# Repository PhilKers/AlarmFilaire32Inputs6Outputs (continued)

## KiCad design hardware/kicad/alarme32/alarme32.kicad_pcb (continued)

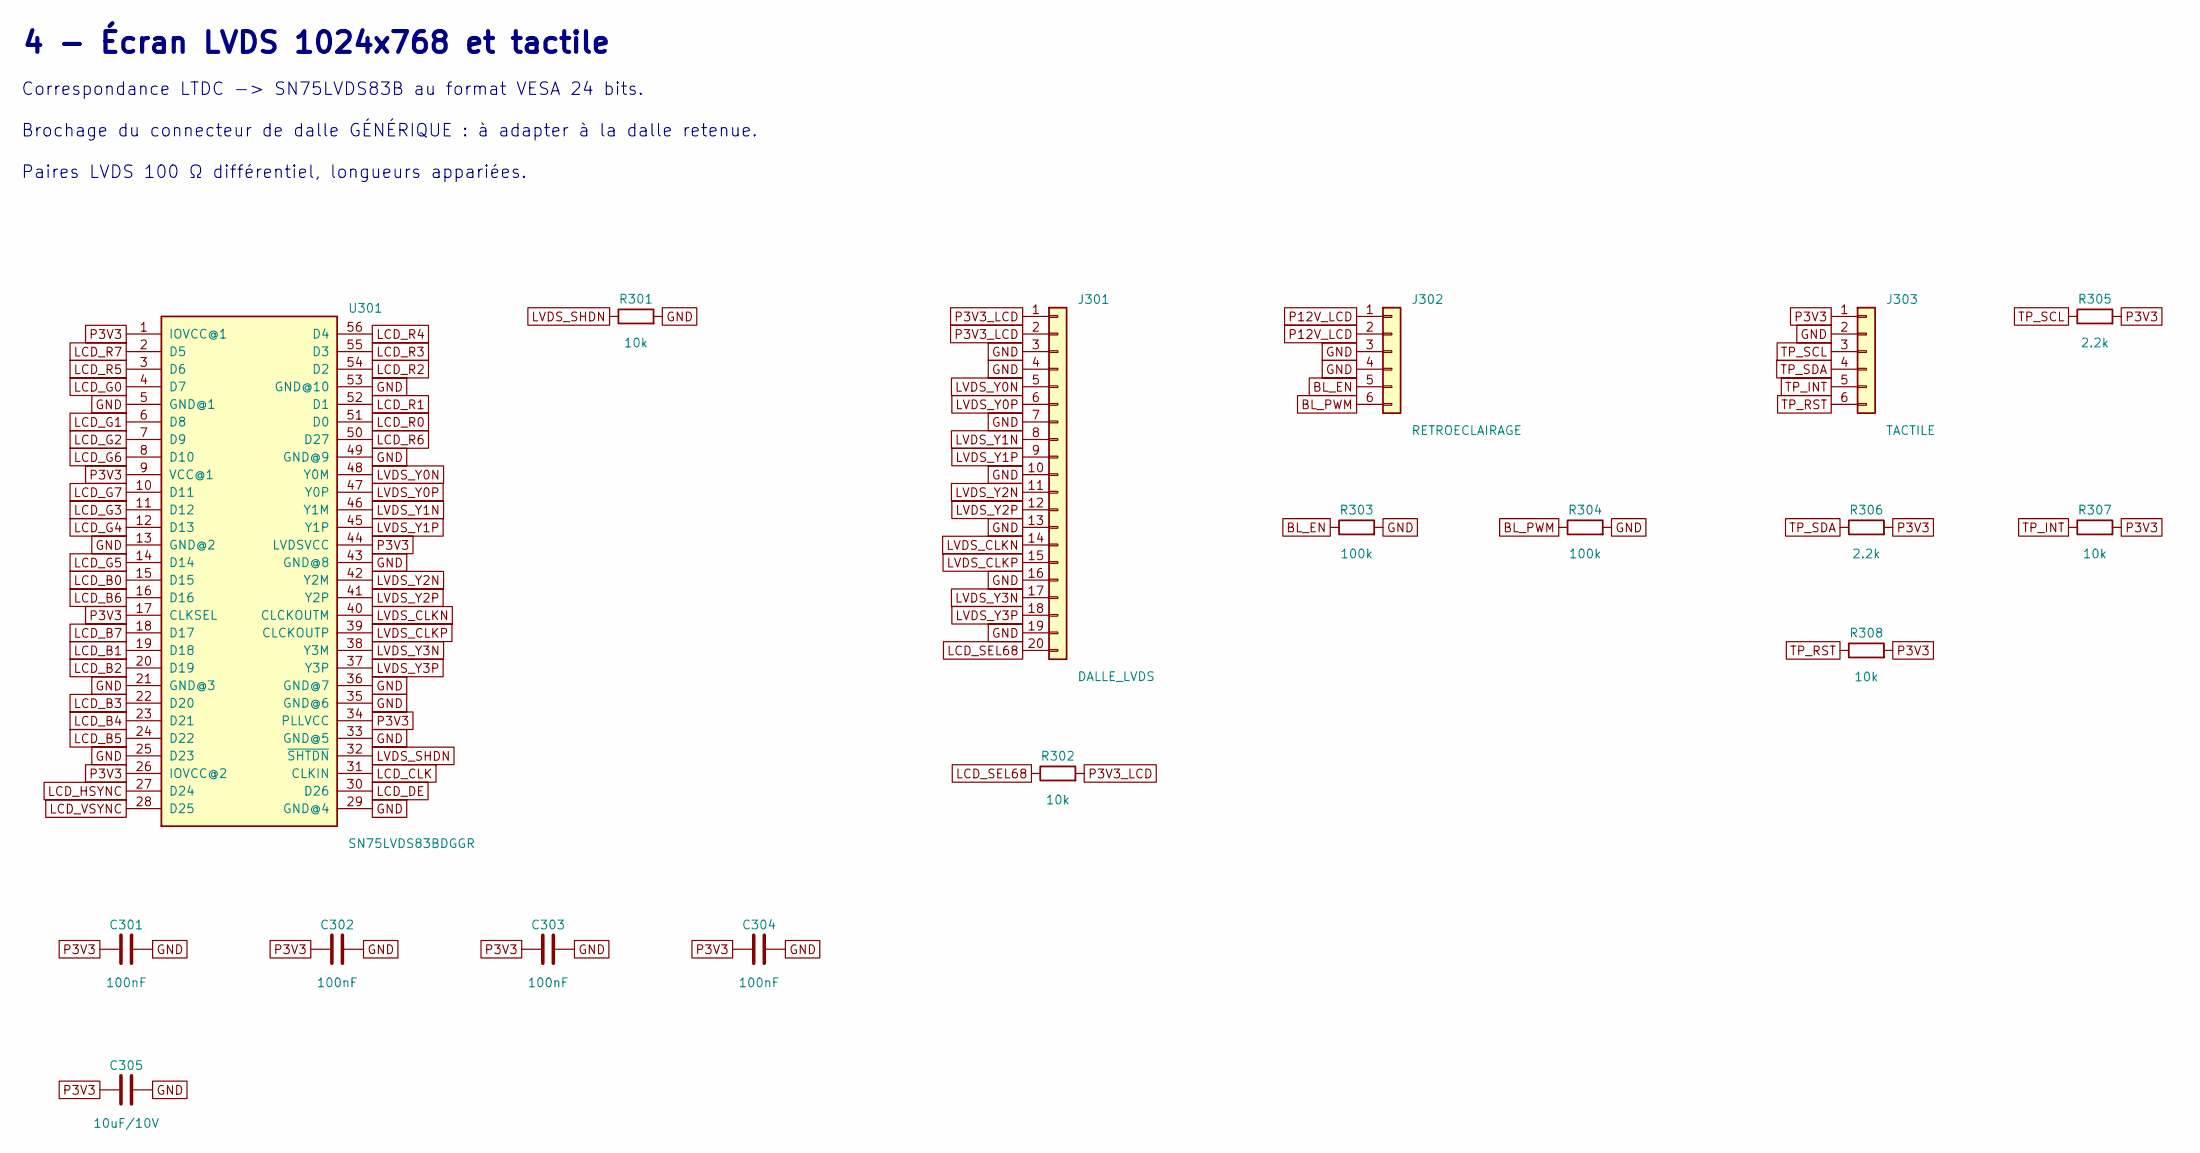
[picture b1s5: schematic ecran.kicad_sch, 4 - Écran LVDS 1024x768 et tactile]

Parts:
C301, C302, C303, C304: 100nF; C_0603_1608Metric
C305: 10uF/10V; C_0805_2012Metric
J301: DALLE_LVDS; TE_2-84952-0_1x20-1MP_P1.0mm_Horizontal
J302: RETROECLAIRAGE; JST_PH_B6B-PH-K_1x06_P2.00mm_Vertical
J303: TACTILE; Hirose_FH12-6S-0.5SH_1x06-1MP_P0.50mm_Horizontal
R301, R302, R307, R308: 10k; R_0603_1608Metric
R303, R304: 100k; R_0603_1608Metric
R305, R306: 2.2k; R_0603_1608Metric
U301: SN75LVDS83BDGGR; TSSOP-56_6.1x14mm_P0.5mm

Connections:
BL_EN: J302.5, R303.1; also elsewhere on the board
BL_PWM: J302.6, R304.1; also elsewhere on the board
GND: C301.2, C302.2, C303.2, C304.2, C305.2, J301.3, J301.4, J301.7, J301.10, J301.13, J301.16, J301.19, J302.3, J302.4, J303.2, R301.2, R303.2, R304.2, U301.5 (GND@1), U301.13 (GND@2), U301.21 (GND@3), U301.25 (D23), U301.29 (GND@4), U301.33 (GND@5), U301.35 (GND@6), U301.36 (GND@7), U301.43 (GND@8), U301.49 (GND@9), U301.53 (GND@10); also elsewhere on the board
LCD_B0: U301.15 (D15); also elsewhere on the board
LCD_B1: U301.19 (D18); also elsewhere on the board
LCD_B2: U301.20 (D19); also elsewhere on the board
LCD_B3: U301.22 (D20); also elsewhere on the board
LCD_B4: U301.23 (D21); also elsewhere on the board
LCD_B5: U301.24 (D22); also elsewhere on the board
LCD_B6: U301.16 (D16); also elsewhere on the board
LCD_B7: U301.18 (D17); also elsewhere on the board
LCD_CLK: U301.31 (CLKIN); also elsewhere on the board
LCD_DE: U301.30 (D26); also elsewhere on the board
LCD_G0: U301.4 (D7); also elsewhere on the board
LCD_G1: U301.6 (D8); also elsewhere on the board
LCD_G2: U301.7 (D9); also elsewhere on the board
LCD_G3: U301.11 (D12); also elsewhere on the board
LCD_G4: U301.12 (D13); also elsewhere on the board
LCD_G5: U301.14 (D14); also elsewhere on the board
LCD_G6: U301.8 (D10); also elsewhere on the board
LCD_G7: U301.10 (D11); also elsewhere on the board
LCD_HSYNC: U301.27 (D24); also elsewhere on the board
LCD_R0: U301.51 (D0); also elsewhere on the board
LCD_R1: U301.52 (D1); also elsewhere on the board
LCD_R2: U301.54 (D2); also elsewhere on the board
LCD_R3: U301.55 (D3); also elsewhere on the board
LCD_R4: U301.56 (D4); also elsewhere on the board
LCD_R5: U301.3 (D6); also elsewhere on the board
LCD_R6: U301.50 (D27); also elsewhere on the board
LCD_R7: U301.2 (D5); also elsewhere on the board
LCD_SEL68: J301.20, R302.1
LCD_VSYNC: U301.28 (D25); also elsewhere on the board
LVDS_CLKN: J301.14, U301.40 (CLCKOUTM)
LVDS_CLKP: J301.15, U301.39 (CLCKOUTP)
LVDS_SHDN: R301.1, U301.32 (~SHTDN); also elsewhere on the board
LVDS_Y0N: J301.5, U301.48 (Y0M)
LVDS_Y0P: J301.6, U301.47 (Y0P)
LVDS_Y1N: J301.8, U301.46 (Y1M)
LVDS_Y1P: J301.9, U301.45 (Y1P)
LVDS_Y2N: J301.11, U301.42 (Y2M)
LVDS_Y2P: J301.12, U301.41 (Y2P)
LVDS_Y3N: J301.17, U301.38 (Y3M)
LVDS_Y3P: J301.18, U301.37 (Y3P)
P3V3: C301.1, C302.1, C303.1, C304.1, C305.1, J303.1, R305.2, R306.2, R307.2, R308.2, U301.1 (IOVCC@1), U301.9 (VCC@1), U301.17 (CLKSEL), U301.26 (IOVCC@2), U301.34 (PLLVCC), U301.44 (LVDSVCC); also elsewhere on the board
P3V3_LCD: J301.1, J301.2, R302.2; also elsewhere on the board
P12V_LCD: J302.1, J302.2; also elsewhere on the board
TP_INT: J303.5, R307.1; also elsewhere on the board
TP_RST: J303.6, R308.1; also elsewhere on the board
TP_SCL: J303.3, R305.1; also elsewhere on the board
TP_SDA: J303.4, R306.1; also elsewhere on the board

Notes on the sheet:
4 - Écran LVDS 1024x768 et tactile
Correspondance LTDC -> SN75LVDS83B au format VESA 24 bits.
Brochage du connecteur de dalle GÉNÉRIQUE : à adapter à la dalle retenue.
Paires LVDS 100 Ω différentiel, longueurs appariées.

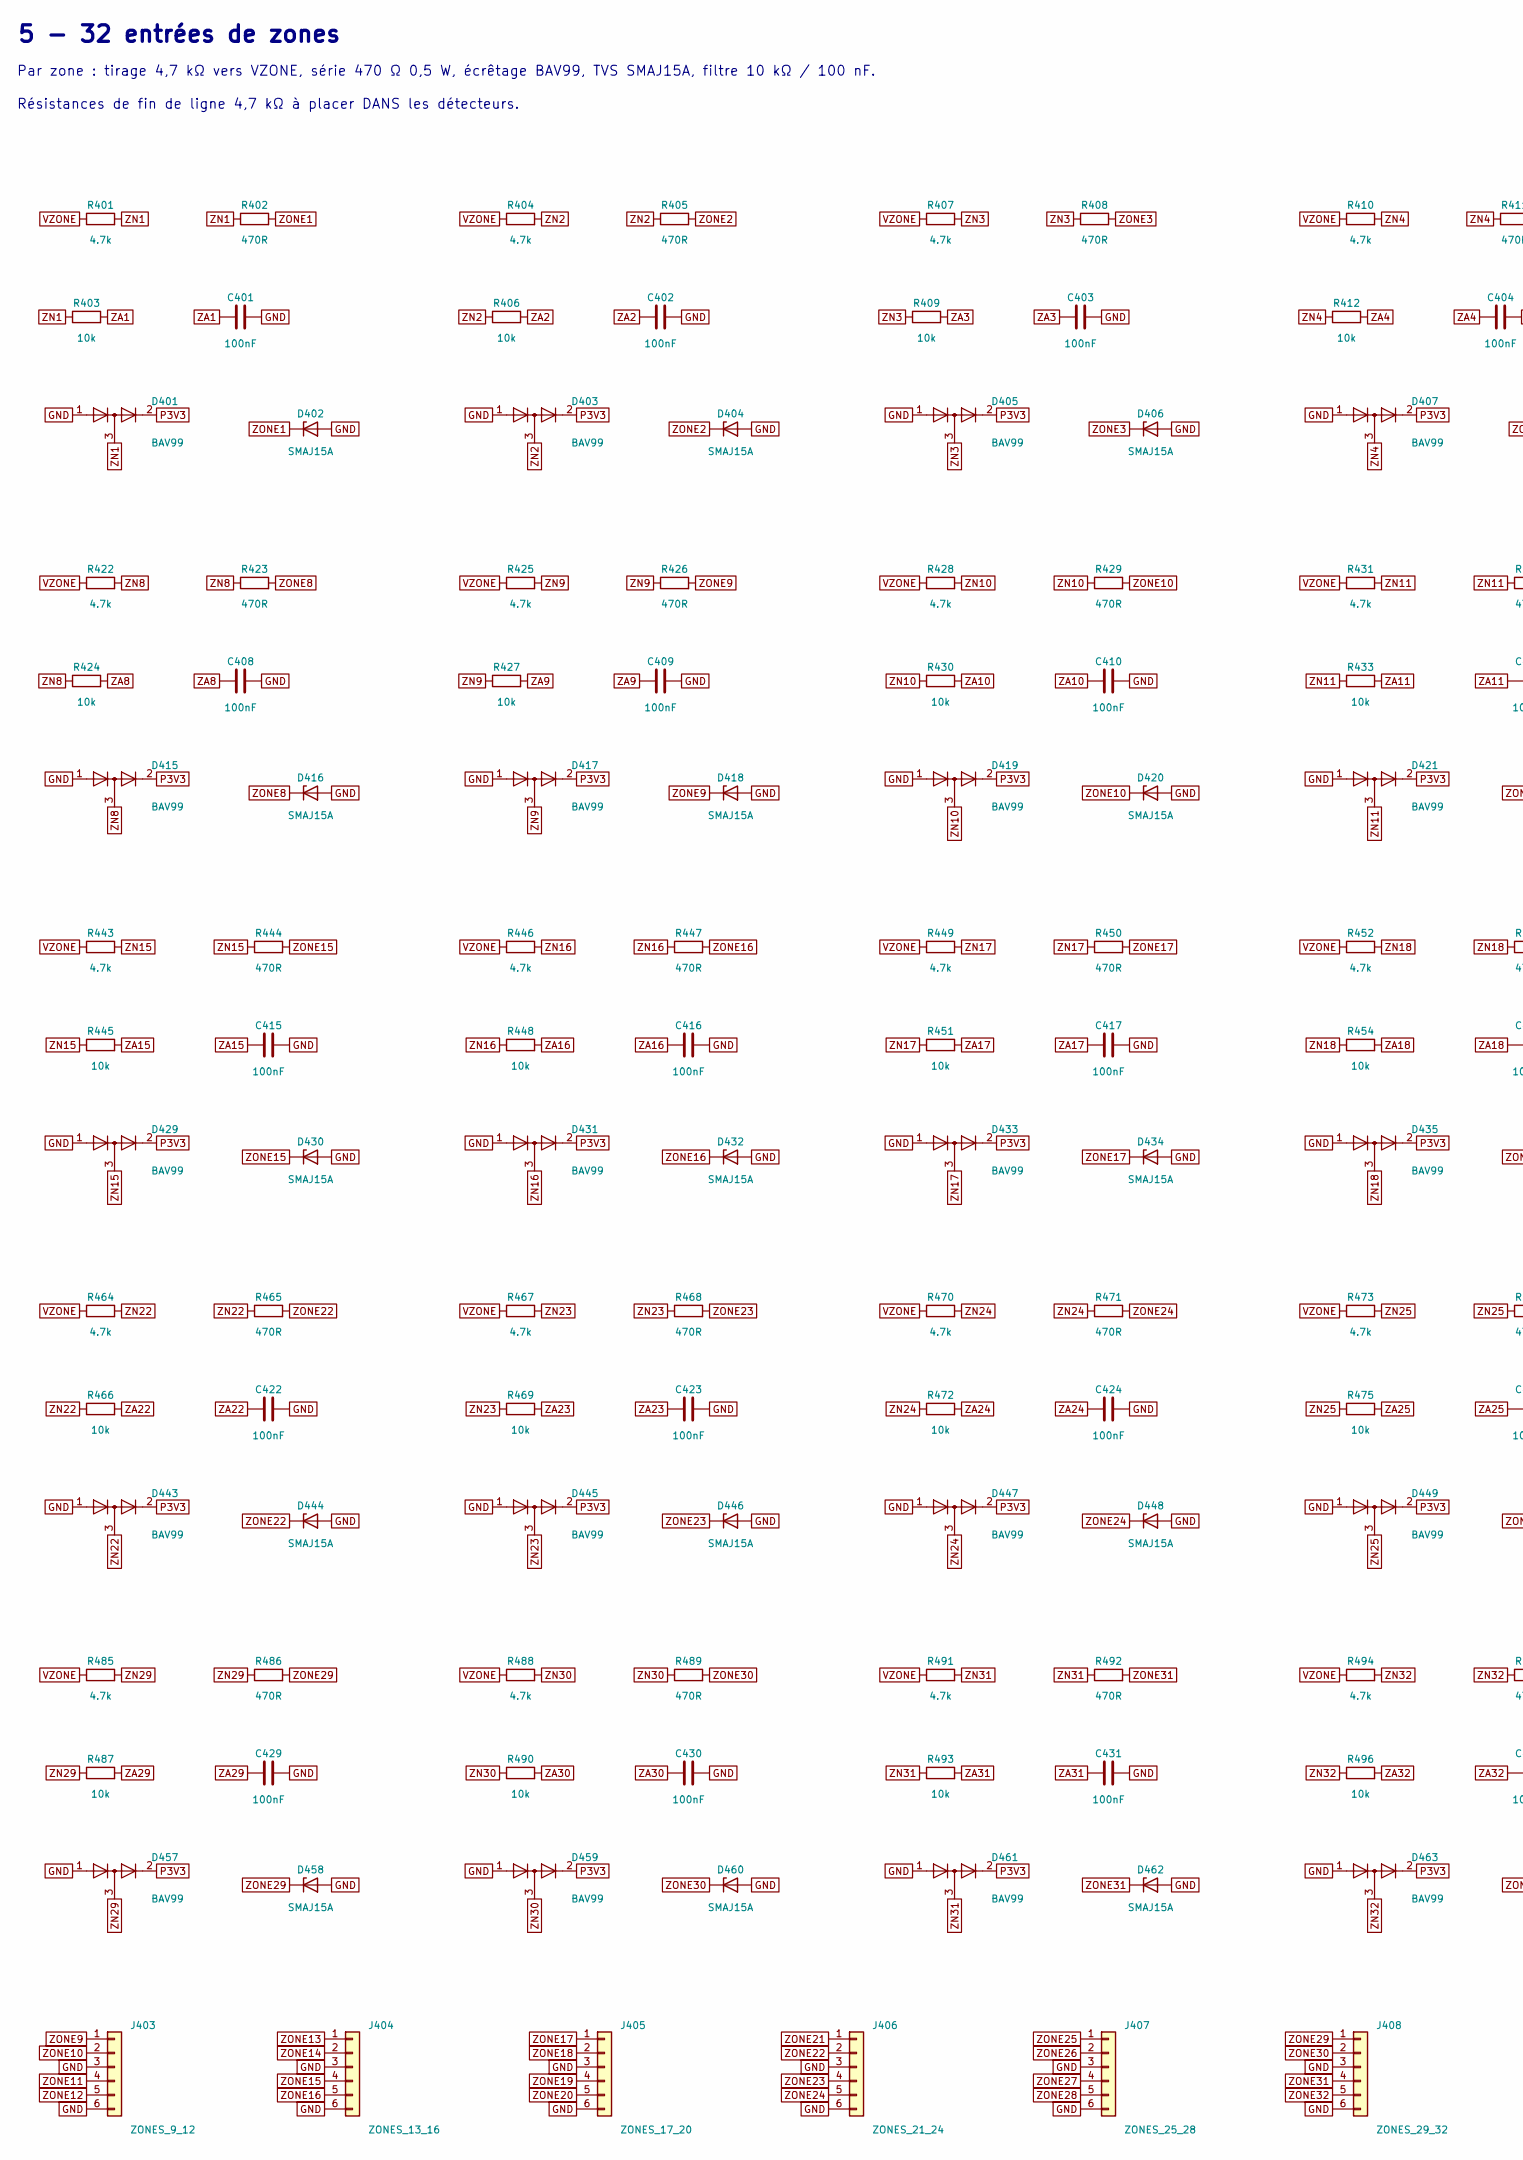
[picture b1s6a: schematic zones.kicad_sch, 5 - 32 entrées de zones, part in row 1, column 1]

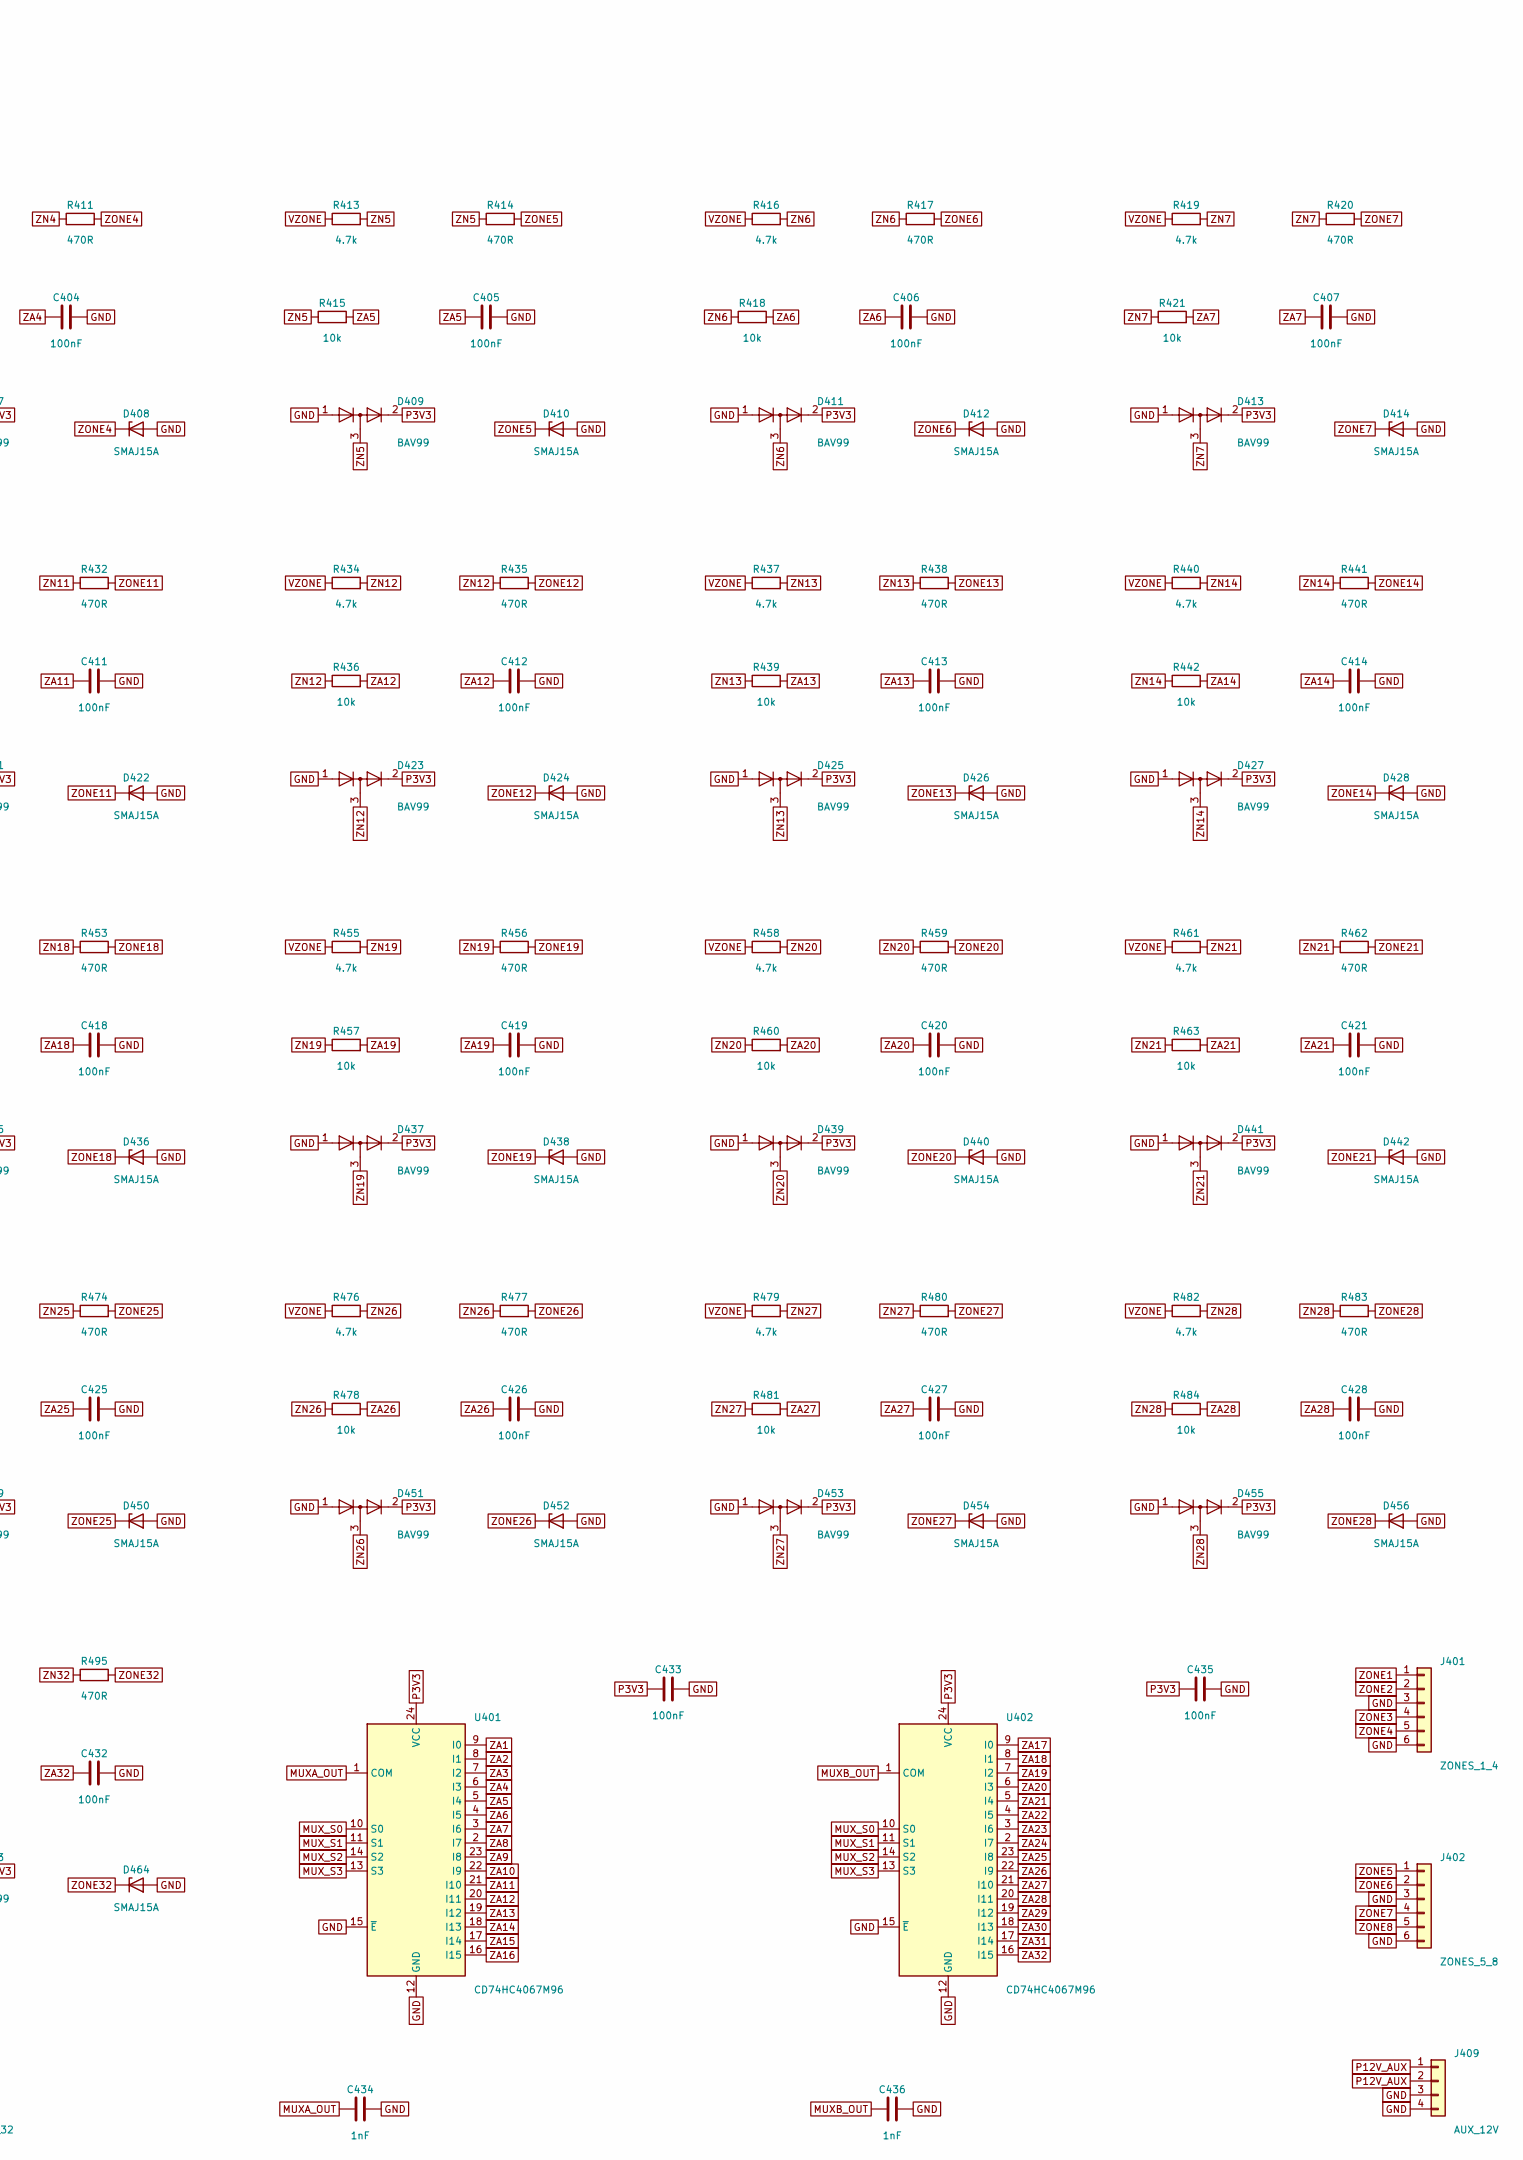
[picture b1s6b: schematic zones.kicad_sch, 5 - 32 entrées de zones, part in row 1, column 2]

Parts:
C401, C402, C403, C404, C405, C406, C407, C408, C409, C410, C411, C412, C413, C414, C415, C416, C417, C418, C419, C420, C421, C422, C423, C424, C425, C426, C427, C428, C429, C430, C431, C432, C433, C435: 100nF; C_0603_1608Metric
C434, C436: 1nF; C_0603_1608Metric
D401, D403, D405, D407, D409, D411, D413, D415, D417, D419, D421, D423, D425, D427, D429, D431, D433, D435, D437, D439, D441, D443, D445, D447, D449, D451, D453, D455, D457, D459, D461, D463: BAV99; SOT-23
D402, D404, D406, D408, D410, D412, D414, D416, D418, D420, D422, D424, D426, D428, D430, D432, D434, D436, D438, D440, D442, D444, D446, D448, D450, D452, D454, D456, D458, D460, D462, D464: SMAJ15A; D_SMA
J401: ZONES_1_4; TerminalBlock_Phoenix_MKDS-1,5-6-5.08_1x06_P5.08mm_Horizont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
J402: ZONES_5_8; TerminalBlock_Phoenix_MKDS-1,5-6-5.08_1x06_P5.08mm_Horizont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
J403: ZONES_9_12; TerminalBlock_Phoenix_MKDS-1,5-6-5.08_1x06_P5.08mm_Horizont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
J404: ZONES_13_16; TerminalBlock_Phoenix_MKDS-1,5-6-5.08_1x06_P5.08mm_Horizont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
J405: ZONES_17_20; TerminalBlock_Phoenix_MKDS-1,5-6-5.08_1x06_P5.08mm_Horizont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
J406: ZONES_21_24; TerminalBlock_Phoenix_MKDS-1,5-6-5.08_1x06_P5.08mm_Horizont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
J407: ZONES_25_28; TerminalBlock_Phoenix_MKDS-1,5-6-5.08_1x06_P5.08mm_Horizont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
J408: ZONES_29_32; TerminalBlock_Phoenix_MKDS-1,5-6-5.08_1x06_P5.08mm_Horizont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
J409: AUX_12V; TerminalBlock_Phoenix_MKDS-1,5-4-5.08_1x04_P5.08mm_Horizont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
R401, R404, R407, R410, R413, R416, R419, R422, R425, R428, R431, R434, R437, R440, R443, R446, R449, R452, R455, R458, R461, R464, R467, R470, R473, R476, R479, R482, R485, R488, R491, R494: 4.7k; R_0603_1608Metric
R402, R405, R408, R411, R414, R417, R420, R423, R426, R429, R432, R435, R438, R441, R444, R447, R450, R453, R456, R459, R462, R465, R468, R471, R474, R477, R480, R483, R486, R489, R492, R495: 470R; R_1206_3216Metric
R403, R406, R409, R412, R415, R418, R421, R424, R427, R430, R433, R436, R439, R442, R445, R448, R451, R454, R457, R460, R463, R466, R469, R472, R475, R478, R481, R484, R487, R490, R493, R496: 10k; R_0603_1608Metric
U401, U402: CD74HC4067M96; SOIC-24W_7.5x15.4mm_P1.27mm

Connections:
GND: C401.2, C402.2, C403.2, C404.2, C405.2, C406.2, C407.2, C408.2, C409.2, C410.2, C411.2, C412.2, C413.2, C414.2, C415.2, C416.2, C417.2, C418.2, C419.2, C420.2, C421.2, C422.2, C423.2, C424.2, C425.2, C426.2, C427.2, C428.2, C429.2, C430.2, C431.2, C432.2, C433.2, C434.2, C435.2, C436.2, D401.1 (K), D402.2 (A), D403.1 (K), D404.2 (A), D405.1 (K), D406.2 (A), D407.1 (K), D408.2 (A), D409.1 (K), D410.2 (A), D411.1 (K), D412.2 (A), D413.1 (K), D414.2 (A), D415.1 (K), D416.2 (A), D417.1 (K), D418.2 (A), D419.1 (K), D420.2 (A), D421.1 (K), D422.2 (A), D423.1 (K), D424.2 (A), D425.1 (K), D426.2 (A), D427.1 (K), D428.2 (A), D429.1 (K), D430.2 (A), D431.1 (K), D432.2 (A), D433.1 (K), D434.2 (A), D435.1 (K), D436.2 (A), D437.1 (K), D438.2 (A), D439.1 (K), D440.2 (A), D441.1 (K), D442.2 (A), D443.1 (K), D444.2 (A), D445.1 (K), D446.2 (A), D447.1 (K), D448.2 (A), D449.1 (K), D450.2 (A), D451.1 (K), D452.2 (A), D453.1 (K), D454.2 (A), D455.1 (K), D456.2 (A), D457.1 (K), D458.2 (A), D459.1 (K), D460.2 (A), D461.1 (K), D462.2 (A), D463.1 (K), D464.2 (A), J401.3, J401.6, J402.3, J402.6, J403.3, J403.6, J404.3, J404.6, J405.3, J405.6, J406.3, J406.6, J407.3, J407.6, J408.3, J408.6, J409.3, J409.4, U401.12 (GND), U401.15 (~E), U402.12 (GND), U402.15 (~E); also elsewhere on the board
MUXA_OUT: C434.1, U401.1 (COM); also elsewhere on the board
MUXB_OUT: C436.1, U402.1 (COM); also elsewhere on the board
MUX_S0: U401.10 (S0), U402.10 (S0); also elsewhere on the board
MUX_S1: U401.11 (S1), U402.11 (S1); also elsewhere on the board
MUX_S2: U401.14 (S2), U402.14 (S2); also elsewhere on the board
MUX_S3: U401.13 (S3), U402.13 (S3); also elsewhere on the board
P3V3: C433.1, C435.1, D401.2 (A), D403.2 (A), D405.2 (A), D407.2 (A), D409.2 (A), D411.2 (A), D413.2 (A), D415.2 (A), D417.2 (A), D419.2 (A), D421.2 (A), D423.2 (A), D425.2 (A), D427.2 (A), D429.2 (A), D431.2 (A), D433.2 (A), D435.2 (A), D437.2 (A), D439.2 (A), D441.2 (A), D443.2 (A), D445.2 (A), D447.2 (A), D449.2 (A), D451.2 (A), D453.2 (A), D455.2 (A), D457.2 (A), D459.2 (A), D461.2 (A), D463.2 (A), U401.24 (VCC), U402.24 (VCC); also elsewhere on the board
P12V_AUX: J409.1, J409.2; also elsewhere on the board
VZONE: R401.1, R404.1, R407.1, R410.1, R413.1, R416.1, R419.1, R422.1, R425.1, R428.1, R431.1, R434.1, R437.1, R440.1, R443.1, R446.1, R449.1, R452.1, R455.1, R458.1, R461.1, R464.1, R467.1, R470.1, R473.1, R476.1, R479.1, R482.1, R485.1, R488.1, R491.1, R494.1; also elsewhere on the board
ZA1: C401.1, R403.2, U401.9 (I0)
ZA2: C402.1, R406.2, U401.8 (I1)
ZA3: C403.1, R409.2, U401.7 (I2)
ZA4: C404.1, R412.2, U401.6 (I3)
ZA5: C405.1, R415.2, U401.5 (I4)
ZA6: C406.1, R418.2, U401.4 (I5)
ZA7: C407.1, R421.2, U401.3 (I6)
ZA8: C408.1, R424.2, U401.2 (I7)
ZA9: C409.1, R427.2, U401.23 (I8)
ZA10: C410.1, R430.2, U401.22 (I9)
ZA11: C411.1, R433.2, U401.21 (I10)
ZA12: C412.1, R436.2, U401.20 (I11)
ZA13: C413.1, R439.2, U401.19 (I12)
ZA14: C414.1, R442.2, U401.18 (I13)
ZA15: C415.1, R445.2, U401.17 (I14)
ZA16: C416.1, R448.2, U401.16 (I15)
ZA17: C417.1, R451.2, U402.9 (I0)
ZA18: C418.1, R454.2, U402.8 (I1)
ZA19: C419.1, R457.2, U402.7 (I2)
ZA20: C420.1, R460.2, U402.6 (I3)
ZA21: C421.1, R463.2, U402.5 (I4)
ZA22: C422.1, R466.2, U402.4 (I5)
ZA23: C423.1, R469.2, U402.3 (I6)
ZA24: C424.1, R472.2, U402.2 (I7)
ZA25: C425.1, R475.2, U402.23 (I8)
ZA26: C426.1, R478.2, U402.22 (I9)
ZA27: C427.1, R481.2, U402.21 (I10)
ZA28: C428.1, R484.2, U402.20 (I11)
ZA29: C429.1, R487.2, U402.19 (I12)
ZA30: C430.1, R490.2, U402.18 (I13)
ZA31: C431.1, R493.2, U402.17 (I14)
ZA32: C432.1, R496.2, U402.16 (I15)
ZN1: D401.3 (K), R401.2, R402.1, R403.1
ZN2: D403.3 (K), R404.2, R405.1, R406.1
ZN3: D405.3 (K), R407.2, R408.1, R409.1
ZN4: D407.3 (K), R410.2, R411.1, R412.1
ZN5: D409.3 (K), R413.2, R414.1, R415.1
ZN6: D411.3 (K), R416.2, R417.1, R418.1
ZN7: D413.3 (K), R419.2, R420.1, R421.1
ZN8: D415.3 (K), R422.2, R423.1, R424.1
ZN9: D417.3 (K), R425.2, R426.1, R427.1
ZN10: D419.3 (K), R428.2, R429.1, R430.1
ZN11: D421.3 (K), R431.2, R432.1, R433.1
ZN12: D423.3 (K), R434.2, R435.1, R436.1
ZN13: D425.3 (K), R437.2, R438.1, R439.1
ZN14: D427.3 (K), R440.2, R441.1, R442.1
ZN15: D429.3 (K), R443.2, R444.1, R445.1
ZN16: D431.3 (K), R446.2, R447.1, R448.1
ZN17: D433.3 (K), R449.2, R450.1, R451.1
ZN18: D435.3 (K), R452.2, R453.1, R454.1
ZN19: D437.3 (K), R455.2, R456.1, R457.1
ZN20: D439.3 (K), R458.2, R459.1, R460.1
ZN21: D441.3 (K), R461.2, R462.1, R463.1
ZN22: D443.3 (K), R464.2, R465.1, R466.1
ZN23: D445.3 (K), R467.2, R468.1, R469.1
ZN24: D447.3 (K), R470.2, R471.1, R472.1
ZN25: D449.3 (K), R473.2, R474.1, R475.1
ZN26: D451.3 (K), R476.2, R477.1, R478.1
ZN27: D453.3 (K), R479.2, R480.1, R481.1
ZN28: D455.3 (K), R482.2, R483.1, R484.1
ZN29: D457.3 (K), R485.2, R486.1, R487.1
ZN30: D459.3 (K), R488.2, R489.1, R490.1
ZN31: D461.3 (K), R491.2, R492.1, R493.1
ZN32: D463.3 (K), R494.2, R495.1, R496.1
ZONE1: D402.1 (K), J401.1, R402.2
ZONE2: D404.1 (K), J401.2, R405.2
ZONE3: D406.1 (K), J401.4, R408.2
ZONE4: D408.1 (K), J401.5, R411.2
ZONE5: D410.1 (K), J402.1, R414.2
ZONE6: D412.1 (K), J402.2, R417.2
ZONE7: D414.1 (K), J402.4, R420.2
ZONE8: D416.1 (K), J402.5, R423.2
ZONE9: D418.1 (K), J403.1, R426.2
ZONE10: D420.1 (K), J403.2, R429.2
ZONE11: D422.1 (K), J403.4, R432.2
ZONE12: D424.1 (K), J403.5, R435.2
ZONE13: D426.1 (K), J404.1, R438.2
ZONE14: D428.1 (K), J404.2, R441.2
ZONE15: D430.1 (K), J404.4, R444.2
ZONE16: D432.1 (K), J404.5, R447.2
ZONE17: D434.1 (K), J405.1, R450.2
ZONE18: D436.1 (K), J405.2, R453.2
ZONE19: D438.1 (K), J405.4, R456.2
ZONE20: D440.1 (K), J405.5, R459.2
ZONE21: D442.1 (K), J406.1, R462.2
ZONE22: D444.1 (K), J406.2, R465.2
ZONE23: D446.1 (K), J406.4, R468.2
ZONE24: D448.1 (K), J406.5, R471.2
ZONE25: D450.1 (K), J407.1, R474.2
ZONE26: D452.1 (K), J407.2, R477.2
ZONE27: D454.1 (K), J407.4, R480.2
ZONE28: D456.1 (K), J407.5, R483.2
ZONE29: D458.1 (K), J408.1, R486.2
ZONE30: D460.1 (K), J408.2, R489.2
ZONE31: D462.1 (K), J408.4, R492.2
ZONE32: D464.1 (K), J408.5, R495.2

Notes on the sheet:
5 - 32 entrées de zones
Par zone : tirage 4,7 kΩ vers VZONE, série 470 Ω 0,5 W, écrêtage BAV99, TVS SMAJ15A, filtre 10 kΩ / 100 nF.
Résistances de fin de ligne 4,7 kΩ à placer DANS les détecteurs.
